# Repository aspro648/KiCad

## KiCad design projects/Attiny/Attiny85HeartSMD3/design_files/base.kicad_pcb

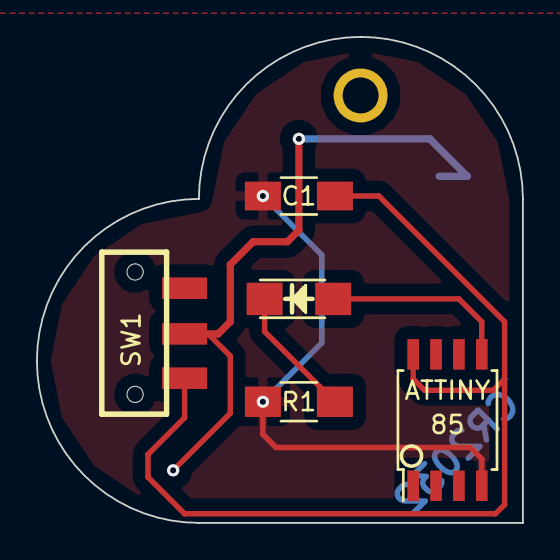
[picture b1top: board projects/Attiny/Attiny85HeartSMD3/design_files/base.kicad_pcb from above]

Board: 2 copper layers, 27.0 x 27.0 mm, 7 parts (1 on the bottom side), 5 nets.

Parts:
ATTINY: ATTINY; SOIJ-8_5.3x5.3mm_Pitch1.27mm
BT1: Battery; BATT_CR2032_SMD
C1: 0.1 uF; C_1206_HandSoldering
D1: LED; LED-1206
P1: CONN_01X01; Pin_Header_Straight_1x01
R1: 330; R_1206_HandSoldering
SW1: SPST; SPST_SMD

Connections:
+BATT: ATTINY.8, C1.2, SW1.1
GND: ATTINY.4, BT1.2, C1.1, R1.2
unnamed: BT1.1, SW1.2
unnamed: ATTINY.5, D1.2
unnamed: D1.1, R1.1

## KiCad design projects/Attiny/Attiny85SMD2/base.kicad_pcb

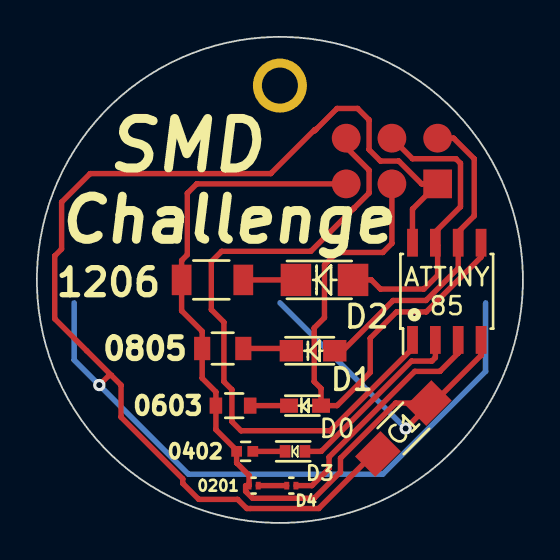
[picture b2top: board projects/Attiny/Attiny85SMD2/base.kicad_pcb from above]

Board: 2 copper layers, 27.0 x 27.0 mm, 15 parts (1 on the bottom side), 13 nets.

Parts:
BT1: Battery; BATT_CR2032_SMD
C1: 0.1 uF; C_1206_HandSoldering
CON1: AVR-ISP-6
D0, D3: LED; LED-0603
D1: LED; LED-0805
D2: LED; LED-1206
D4: LED; R_0201
IC1: ATTINY85-S; SOIC-8_3.9x4.9mm_Pitch1.27mm
P1: CONN_01X01; Pin_Header_Straight_1x01
R0: 330; R_0603
R1: 330; R_0805
R2: 330; R_1206
R3: 330; R_0402
R4: 330; R_0201

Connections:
+BATT: BT1.1, C1.2, CON1.2, IC1.8
GND: BT1.2, C1.1, CON1.6, IC1.4, R0.2, R1.2, R2.2, R3.2, R4.2
unnamed: CON1.1, D1.2, IC1.6
unnamed: CON1.3, D2.2, IC1.7
unnamed: CON1.4, D0.2, IC1.5
unnamed: CON1.5, IC1.1
unnamed: D0.1, R0.1
unnamed: D1.1, R1.1
unnamed: D2.1, R2.1
unnamed: D3.1, R3.1
unnamed: D3.2, IC1.2
unnamed: D4.1, R4.1
unnamed: D4.2, IC1.3

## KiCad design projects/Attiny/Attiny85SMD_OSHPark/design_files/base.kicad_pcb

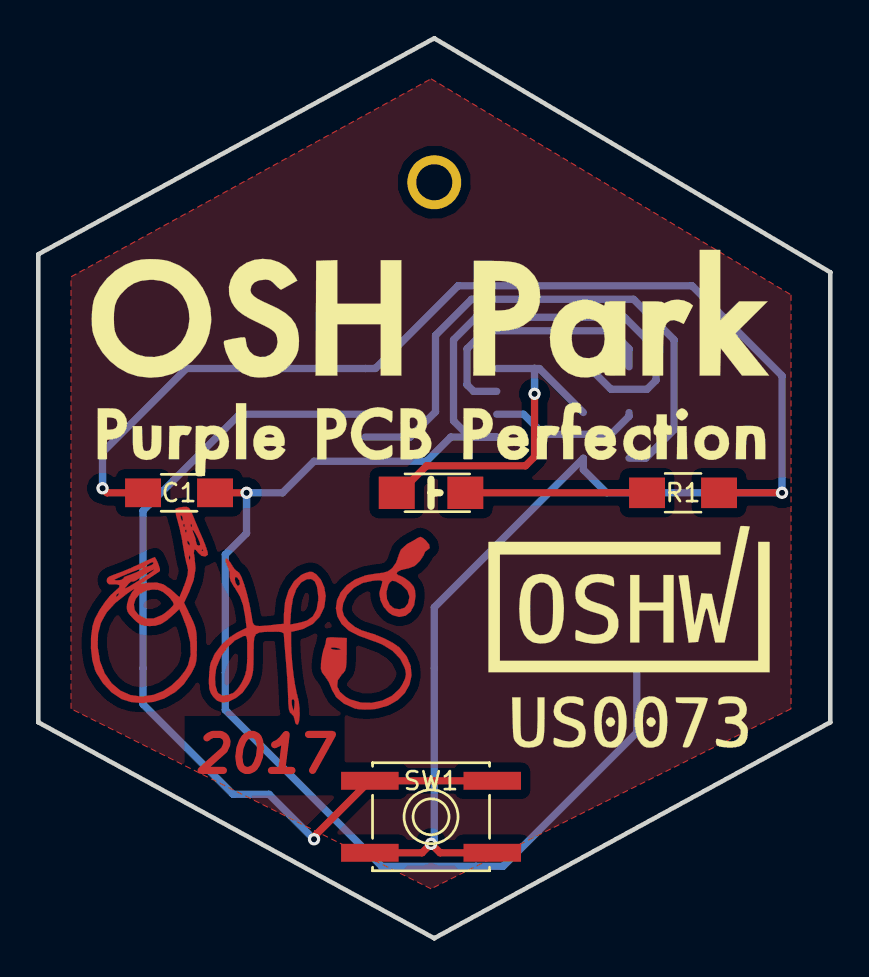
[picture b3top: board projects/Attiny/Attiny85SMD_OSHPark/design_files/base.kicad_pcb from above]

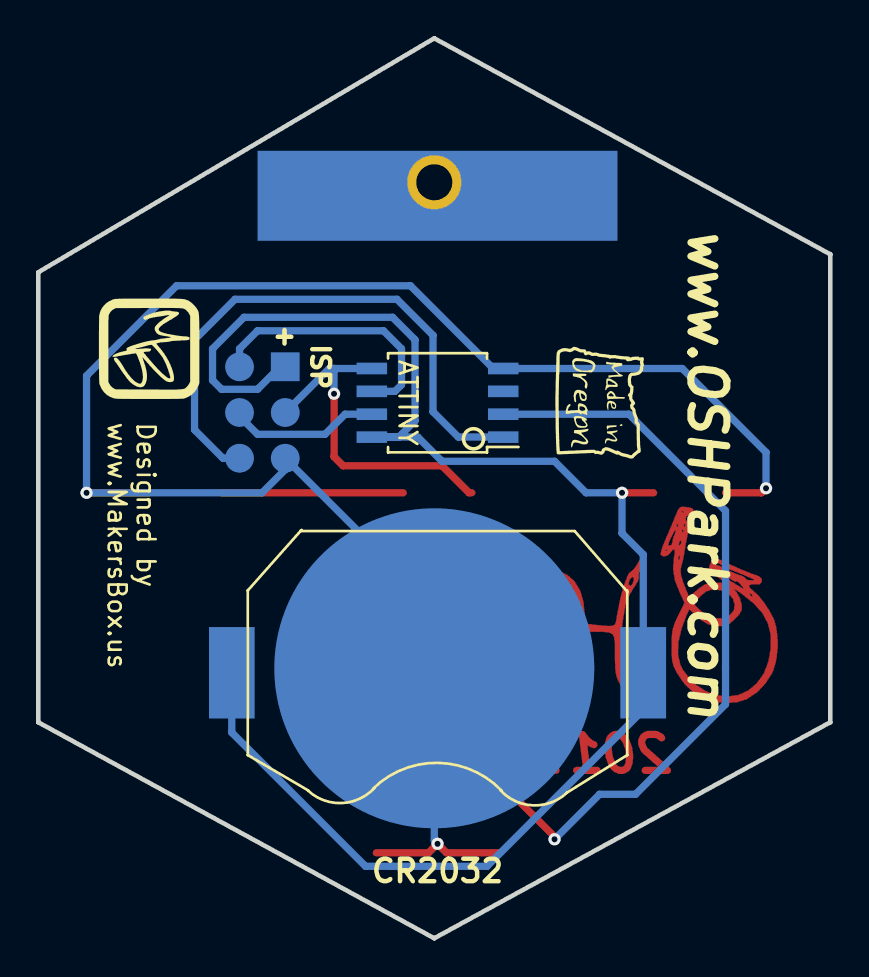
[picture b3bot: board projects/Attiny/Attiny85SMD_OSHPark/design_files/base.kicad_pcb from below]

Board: 2 copper layers, 44.0 x 50.0 mm, 10 parts (3 on the bottom side), 8 nets.

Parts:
ATTINY: ATTINY; SOIJ-8_5.3x5.3mm_Pitch1.27mm
BT1: Battery; BATT_CR2032_SMD
C1: 0.1 uF; C_1206_HandSoldering
CON1: AVR-ISP-6
D1: LED; LED-1206
P1: CONN_01X01; Pin_Header_Straight_1x01
R1: 330; R_1206_HandSoldering
SW1: SW_PUSH; SW_SPST_EVQP0
VAL: MB225rev
VAL#2: MadeInOregonRev25

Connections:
+BATT: ATTINY.8, BT1.1, C1.2, CON1.2
GND: ATTINY.4, BT1.2, C1.1, CON1.6, R1.2, SW1.2
unnamed: ATTINY.6, CON1.1
unnamed: ATTINY.7, CON1.3
unnamed: ATTINY.5, CON1.4, D1.2
unnamed: ATTINY.1, CON1.5
unnamed: D1.1, R1.1
unnamed: ATTINY.2, SW1.1

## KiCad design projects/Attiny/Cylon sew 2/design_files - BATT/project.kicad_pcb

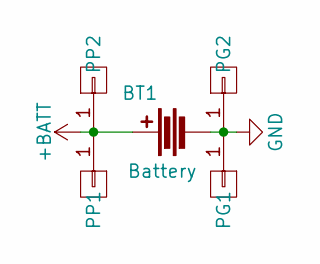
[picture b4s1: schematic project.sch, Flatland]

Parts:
BT1: Battery; BATT_CR2032_SMD
PG1, PG2: CONN_01X01; SolderWirePad_single_1-5mmDrill
PP1, PP2: CONN_01X01; SolderWirePad_single_1-5mmDrill

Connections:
+BATT: BT1.1, PP1.1, PP2.1
GND: BT1.2, PG1.1, PG2.1

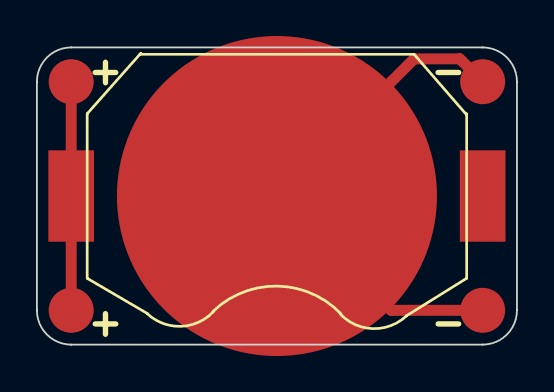
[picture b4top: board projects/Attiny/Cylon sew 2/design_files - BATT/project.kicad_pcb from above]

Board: 2 copper layers, 26.7 x 16.5 mm, 5 parts (0 on the bottom side), 2 nets.

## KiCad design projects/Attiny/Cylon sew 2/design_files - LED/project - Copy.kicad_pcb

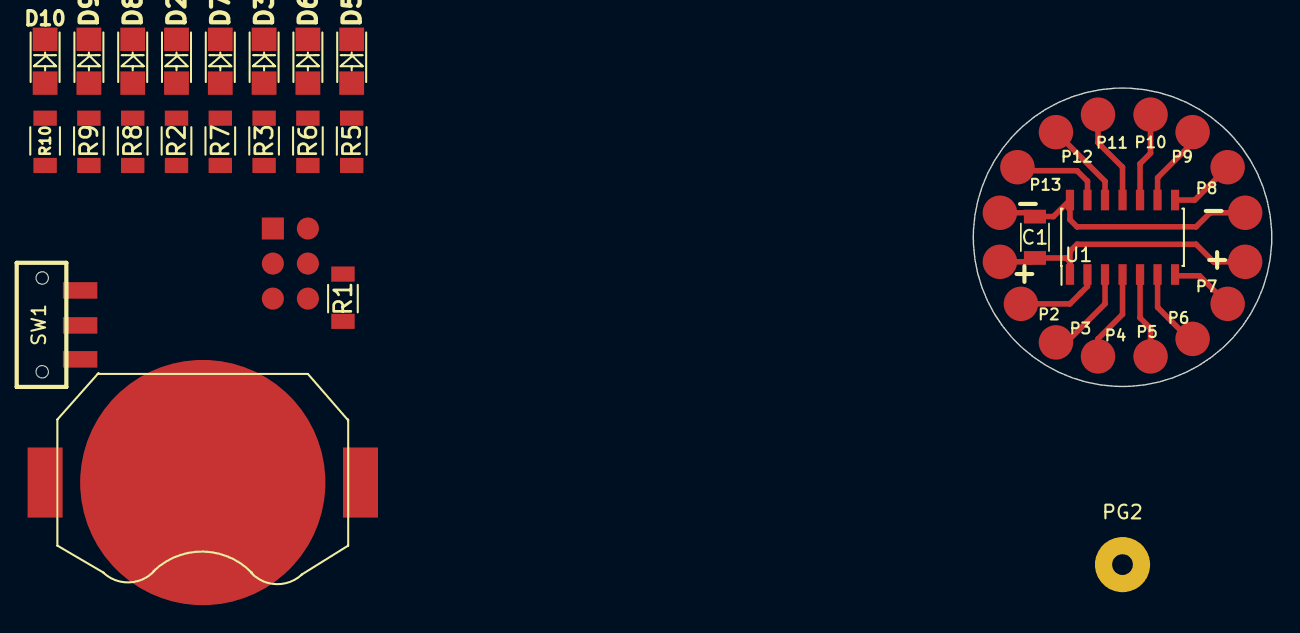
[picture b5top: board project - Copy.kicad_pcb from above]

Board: 2 copper layers, 21.6 x 21.6 mm, 39 parts (0 on the bottom side), 24 nets.

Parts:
BT1: Battery; BATT_CR2032_SMD
C1: 0.1 uF; C_1206
CON1: AVR-ISP-6
D2, D3, D5, D6, D7, D8, D9, D10: LED; LED-1206
P1, P2, P3, P4, P5, P6, P7, P8, P9, P10, P11, P12, P13, P14: CONN_01X01; Pad
PG1: CONN_01X01; Pad
PG2: CONN_01X01; SolderWirePad_single_1-5mmDrill
PP1: CONN_01X01; Pad
R1: 0; R_1206
R2, R3, R5, R6, R7, R8, R9, R10: 100; R_1206
SW1: SW_SPDT; SPST_SMD
U1: ATTINY84A-SSU; SOIC-14_3.9x8.7mm_Pitch1.27mm

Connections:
+BATT: C1.1, P1.1, PP1.1, R1.2, SW1.3, U1.1
/D0: P2.1, U1.2
/D1: P3.1, U1.3
/D2: P5.1, R2.1, U1.5
/D3: P6.1, R3.1, U1.6
/D4-MOSI: CON1.4, P7.1, U1.7
/D5-MISO: CON1.1, P8.1, R5.1, U1.8
/D6-SCK: CON1.3, P9.1, R6.1, U1.9
/D7: P10.1, R7.1, U1.10
/D8: P11.1, R8.1, U1.11
/D9: P12.1, R9.1, U1.12
/D10: P13.1, R10.1, U1.13
/RESET: CON1.5, P4.1, U1.4
GND: BT1.2, C1.2, CON1.6, D2.1, D3.1, D5.1, D6.1, D7.1, D8.1, D9.1, D10.1, P14.1, PG1.1, PG2.1, U1.14
unnamed: BT1.1, SW1.1
unnamed: CON1.2, R1.1
unnamed: D2.2, R2.2
unnamed: D3.2, R3.2
unnamed: D5.2, R5.2
unnamed: D6.2, R6.2
unnamed: D7.2, R7.2
unnamed: D8.2, R8.2
unnamed: D9.2, R9.2
unnamed: D10.2, R10.2

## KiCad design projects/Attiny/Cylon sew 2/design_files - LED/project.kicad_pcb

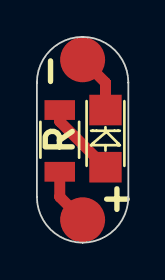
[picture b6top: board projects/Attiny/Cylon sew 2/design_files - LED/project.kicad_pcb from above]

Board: 2 copper layers, 5.1 x 11.4 mm, 4 parts (0 on the bottom side), 3 nets.

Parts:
D5: LED; LED-1206
P8, P14: CONN_01X01; Pad
R5: 100; R_1206

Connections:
/D5-MISO: P8.1, R5.1
GND: D5.1, P14.1
unnamed: D5.2, R5.2
